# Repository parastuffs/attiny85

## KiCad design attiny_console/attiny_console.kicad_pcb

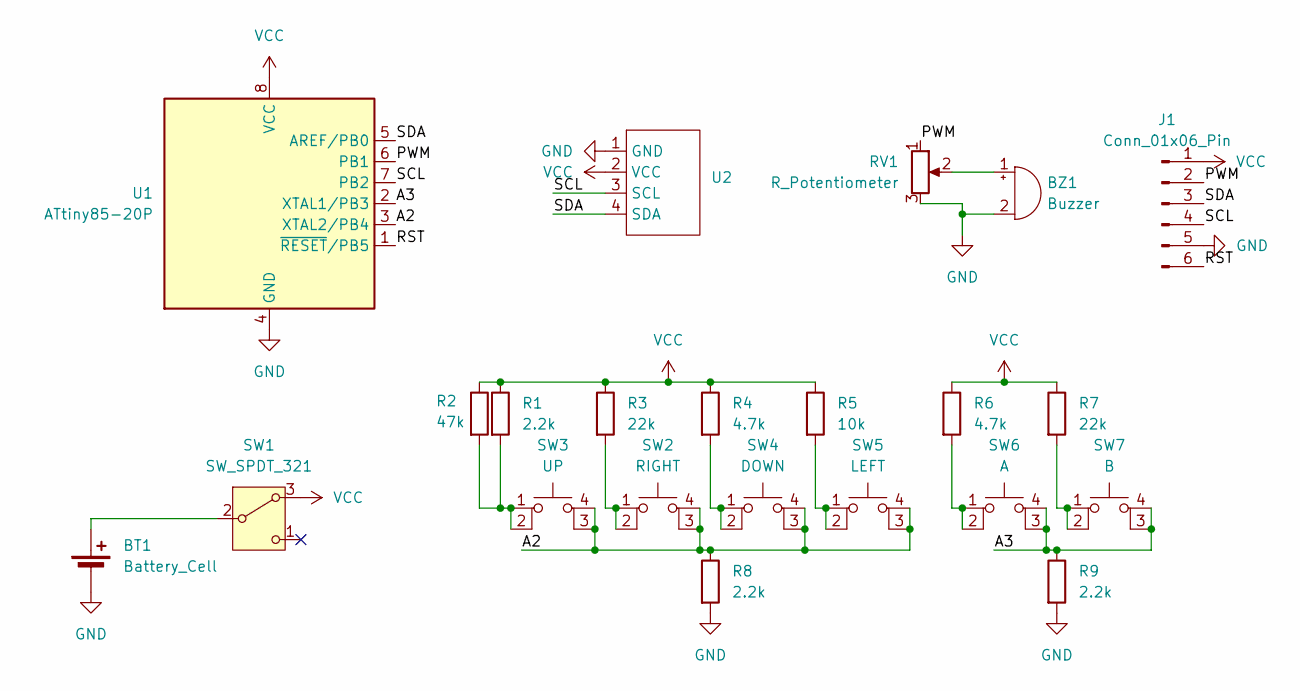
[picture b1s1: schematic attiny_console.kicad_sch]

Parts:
BT1: Battery_Cell; Battery_Panasonic_CR2032-HFN_Horizontal_CircularHoles
BZ1: Buzzer; MagneticBuzzer_ProSignal_ABT-410-RC
J1: Conn_01x06_Pin; PinHeader_1x06_P2.54mm_Vertical
R1, R8, R9: 2.2k; R_Axial_DIN0207_L6.3mm_D2.5mm_P10.16mm_Horizontal
R2: 47k; R_Axial_DIN0207_L6.3mm_D2.5mm_P10.16mm_Horizontal
R3, R7: 22k; R_Axial_DIN0207_L6.3mm_D2.5mm_P10.16mm_Horizontal
R4, R6: 4.7k; R_Axial_DIN0207_L6.3mm_D2.5mm_P10.16mm_Horizontal
R5: 10k; R_Axial_DIN0207_L6.3mm_D2.5mm_P10.16mm_Horizontal
RV1: R_Potentiometer; Gear Dial Potentiometer
SW1: SW_SPDT_321; SW_Slide_SPDT_Angled_CK_OS102011MA1Q
SW2: RIGHT; button_tactile_silicone
SW3: UP; button_tactile_silicone
SW4: DOWN; button_tactile_silicone
SW5: LEFT; button_tactile_silicone
SW6: A; button_tactile_silicone
SW7: B; button_tactile_silicone
U1: ATtiny85-20P; DIP-8_W7.62mm
U2: OLED_0.96

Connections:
/A2: R8.1, SW2.3 (K), SW2.4 (A), SW3.3 (K), SW3.4 (A), SW4.3 (K), SW4.4 (A), SW5.3 (K), SW5.4 (A), U1.3 (XTAL2/PB4)
/A3: R9.1, SW6.3 (K), SW6.4 (A), SW7.3 (K), SW7.4 (A), U1.2 (XTAL1/PB3)
/PWM: J1.2, RV1.1, U1.6 (PB1)
/RST: J1.6, U1.1 (~RESET/PB5)
/SCL: J1.4, U1.7 (PB2), U2.3 (SCL)
/SDA: J1.3, U1.5 (AREF/PB0), U2.4 (SDA)
GND: BT1.2 (-), BZ1.2 (-), J1.5, R8.2, R9.2, RV1.3, U1.4 (GND), U2.1 (GND)
unnamed: BT1.1 (+), SW1.2 (B)
unnamed: BZ1.1 (+), RV1.2
unnamed: R1.2, R2.2, SW3.1, SW3.2
unnamed: R3.2, SW2.1, SW2.2
unnamed: R4.2, SW4.1, SW4.2
unnamed: R5.2, SW5.1, SW5.2
unnamed: R6.2, SW6.1, SW6.2
unnamed: R7.2, SW7.1, SW7.2
VCC: J1.1, R1.1, R2.1, R3.1, R4.1, R5.1, R6.1, R7.1, SW1.3 (A), U1.8 (VCC), U2.2 (VCC)

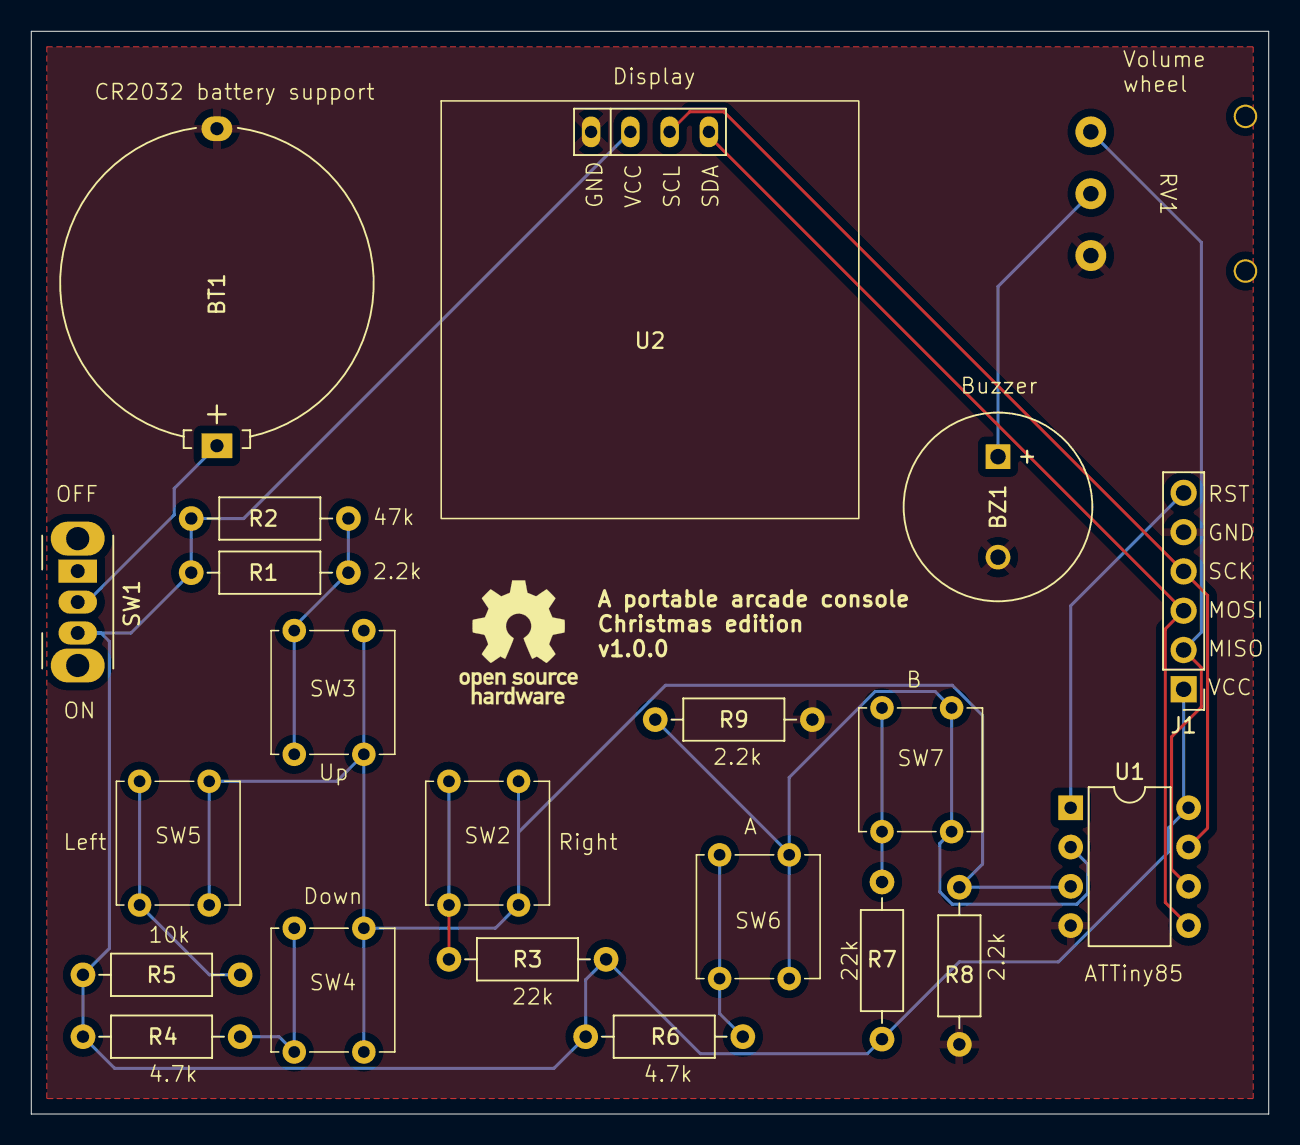
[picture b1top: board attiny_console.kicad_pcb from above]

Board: 2 copper layers, 80.0 x 70.0 mm, 22 parts (0 on the bottom side), 16 nets.

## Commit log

2024-12-01 [PCB v1.0.0]
